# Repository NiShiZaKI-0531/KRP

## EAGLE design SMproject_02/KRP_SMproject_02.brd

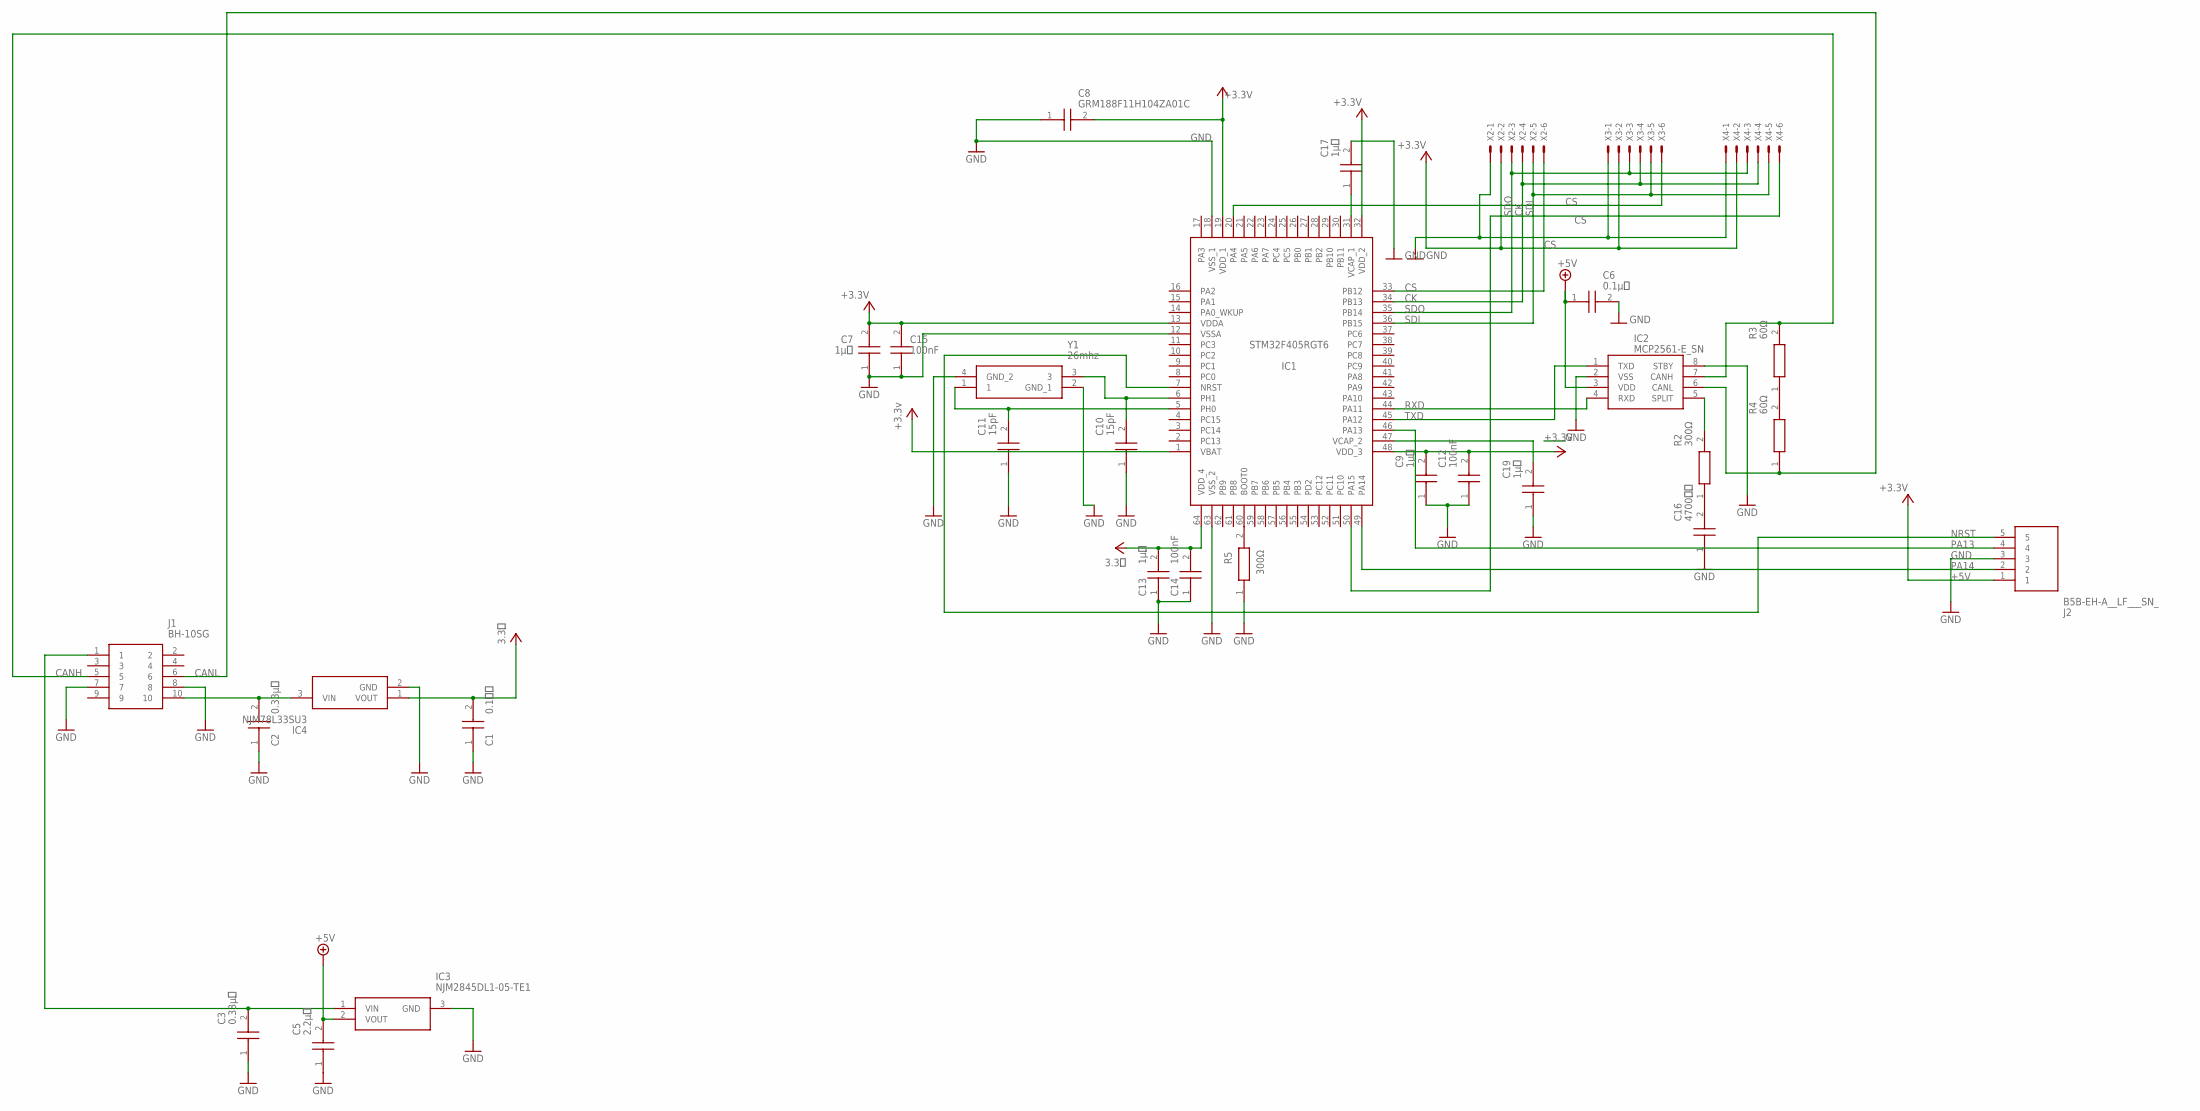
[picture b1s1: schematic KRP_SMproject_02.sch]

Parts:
C1: 0.1ｐｆ; CAPC1608X90N
C2, C3: 0.33μｆ; CAPC1608X90N
C5: 2.2μｆ; CAPC1608X90N
C6: 0.1μｆ; CAPC1608X90N
C7, C9, C13, C17, C19: 1μｆ; CAPC1608X90N
C8: GRM188F11H104ZA01C; CAPC1608X90N
C10, C11: 15pF; CAPC1608X90N
C12, C14, C15: 100nF; CAPC1608X90N
C16: 4700ｐＦ; CAPC1608X90N
IC1: STM32F405RGT6; QFP50P1200X1200X160-64N
IC2: MCP2561-E_SN; SOIC127P600X175-8N
IC3: NJM2845DL1-05-TE1; TO-252-3-L1
IC4: NJM78L33SU3; SOT-89-3
J1: BH-10SG; SHDR10W64P254_2X5_2032X910X935
J2: B5B-EH-A__LF___SN_; SHDR5W64P0X250_1X5_1500X380X60
R2, R5: 300Ω; RESC1608X50N
R3, R4: 60Ω; RESC1608X50N
X2, X3, X4: 22-23-2061
Y1: 26mhz; FA128

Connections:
+5V: C1.2, C5.2, C6.1, C7.2, C8.2, C9.2, C12.2, C13.2, C14.2, C15.2, IC1.1 (VBAT), IC1.13 (VDDA), IC1.19 (VDD_1), IC1.32 (VDD_2), IC1.48 (VDD_3), IC1.64 (VDD_4), IC2.3 (VDD), IC3.2 (VOUT), IC4.1 (VOUT), J2.1, X2.2, X3.2, X4.2
CANH: IC2.7 (CANH), J1.5, R3.2
CANL: IC2.6 (CANL), J1.6, R4.1
CK: IC1.34 (PB13), X2.4, X3.4, X4.4
CS: IC1.20 (PA4), IC1.33 (PB12), IC1.50 (PA15), X2.6, X3.6, X4.6
GND: C1.1, C2.1, C3.1, C5.1, C6.2, C7.1, C8.1, C9.1, C10.1, C11.1, C12.1, C13.1, C14.1, C15.1, C16.1, C17.2, C19.1, IC1.12 (VSSA), IC1.18 (VSS_1), IC1.63 (VSS_2), IC2.2 (VSS), IC2.8 (STBY), IC3.3 (GND), IC4.2 (GND), J1.7, J1.8, J2.3, R5.1, X2.1, X3.1, X4.1, Y1.2 (GND_1), Y1.4 (GND_2)
unnamed: C2.2, IC4.3 (VIN), J1.10
unnamed: C3.2, IC3.1 (VIN), J1.1
unnamed: IC2.5 (SPLIT), R2.2
unnamed: C16.2, R2.1
unnamed: C11.2, IC1.5 (PH0), Y1.1
unnamed: C10.2, IC1.6 (PH1), Y1.3
unnamed: IC1.60 (BOOT0), R5.2
unnamed: C17.1, IC1.31 (VCAP_1)
unnamed: C19.2, IC1.47 (VCAP_2)
unnamed: R3.1, R4.2
NRST: IC1.7 (NRST), J2.5
PA13: IC1.46 (PA13), J2.4
PA14: IC1.49 (PA14), J2.2
RXD: IC1.44 (PA11), IC2.4 (RXD)
SDI: IC1.36 (PB15), X2.5, X3.5, X4.5
SDO: IC1.35 (PB14), X2.3, X3.3, X4.3
TXD: IC1.45 (PA12), IC2.1 (TXD)

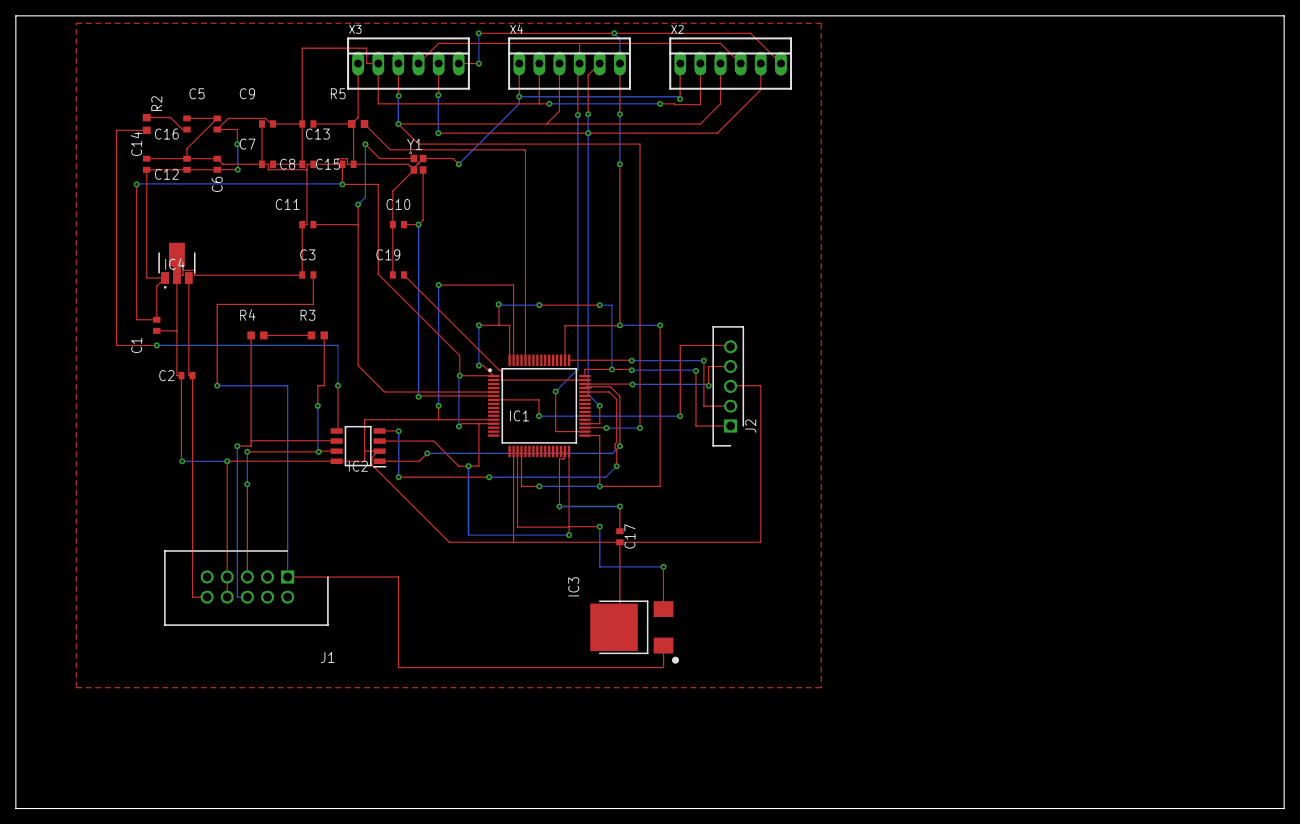
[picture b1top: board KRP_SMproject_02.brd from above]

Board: 2 copper layers, 160.0 x 100.0 mm, 31 parts (0 on the bottom side), 23 nets.

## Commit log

2020-03-24 test
2020-04-05 second
2020-04-06 third
2020-04-14 last
